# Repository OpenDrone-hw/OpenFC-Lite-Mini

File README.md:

# OpenFC Lite 20x20

Open source Betaflight flight controller built on the RP2354A, 20 x 20 mm
mounting pattern, part of the incutec OpenDrone line.

## Specifications

| | |
|---|---|
| Firmware | Betaflight |
| MCU | RP2354A |
| IMU | BMI270 |
| Barometer | None |
| Blackbox | microSD |
| OSD | Analog and digital |
| UARTs | 3 |
| General-purpose I/O | 4 PWM-capable pins (GPIO22-25) on the 8-pin connector; the Betaflight target runs bidirectional DShot on them |
| RX | External, CRSF or SBUS |
| Input | 3-6S* LiPo (9.0-25.2 V) |
| BEC | 10 V switchable + 5 V always-on, 3 A |
| Current sense | Yes |
| USB | USB-C |
| Mounting | 20 x 20 mm, 3.0 mm holes |
| Dimensions | 26.9 x 26.9 mm |
| PCB | 6-layer, 1.6 mm |

* Also runs on 2S; the 10 V VTX output then follows the battery voltage instead of holding 10 V.

Technical write-up, part list and layout constraints: [AGENTS.md](AGENTS.md).

## Firmware

Betaflight, target `OPENFC_LITE_MINI_RP2350A`. The current image is in
[`firmware/`](firmware/); older ones are in `firmware/archive/`.

Boards flashed before 2026-10-25 show no analog OSD while the LED strip
feature is on, and a WS2812 strip on the LED pad shows wrong colours. The
current image fixes both. To update:

1. In Betaflight Configurator, CLI tab: run `diff all` and save the output.
2. Run `bl rom`. The board reboots as a USB drive named `RP2350`.
3. Copy the `.uf2` from `firmware/` onto that drive. The board restarts on
   its own.
4. Reconnect and check your settings; paste the saved `diff all` back if
   anything is missing.

Without updating, `feature -LED_STRIP` then `save` in the CLI brings the
OSD back (the LED strip is then off).

## In the line

What pairs with what, and what is available:
[opendrone.be](https://opendrone.be).

## Contributing

See [CONTRIBUTING.md](CONTRIBUTING.md).

## License

Hardware licensed under [CERN-OHL-S-2.0](https://ohwr.org/cern_ohl_s_v2.txt),
see [LICENSE](LICENSE).

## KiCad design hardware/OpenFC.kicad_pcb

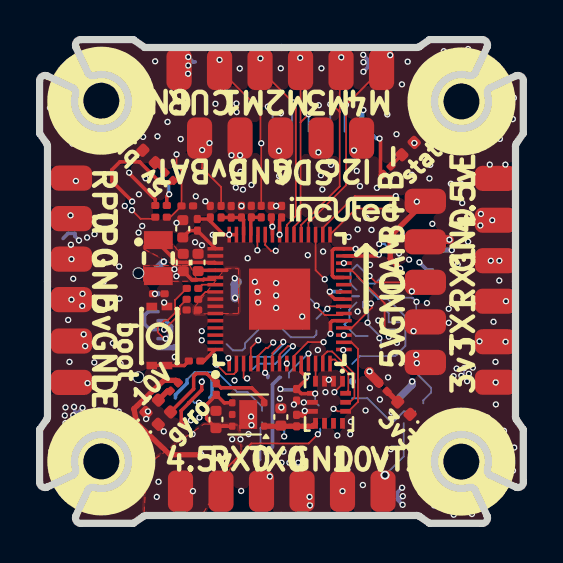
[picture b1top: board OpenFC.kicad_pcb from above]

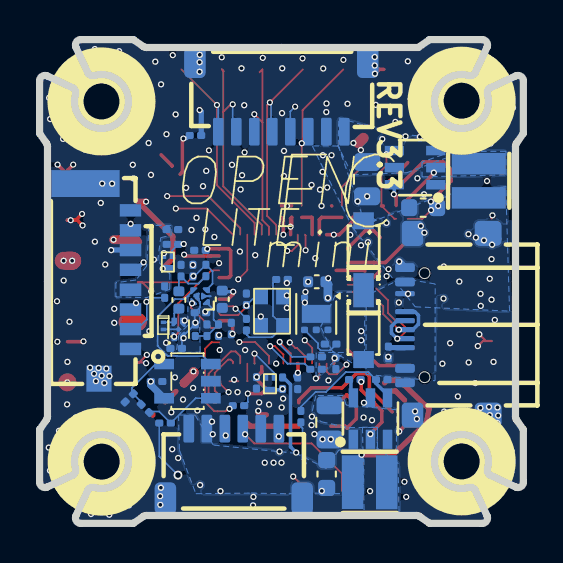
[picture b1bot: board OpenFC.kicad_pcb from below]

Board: 6 copper layers, 26.9 x 26.9 mm, 131 parts (58 on the bottom side), 75 nets.

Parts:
C1, C3, C4, C5, C7, C8, C9, C11, C12, C13, C22, C26, C27, C32, C35, C36, C39, C41, C42, C43: 100n; C_0201_0603Metric
C6, C10: 20p; C_0201_0603Metric
C24, C25: 4.7uF 50v; C_0805_2012Metric
C28, C29: 22uF; C_0603_1608Metric
C31, C37, C44, C45, C46: 4.7uF; C_0402_1005Metric
C33, C34: 22uF; C_0402_1005Metric
C38: 470p; C_0201_0603Metric
C40: 1uF; C_0402_1005Metric
Card1: TF-021B-H265; TF-SMD_TF-021B-H265
D2: LED_1_Blue; LED_0402_1005Metric
D4, D5, D7, D8: LED_1_Green; LED_0402_1005Metric
D6, D10: DSK24; SOD-123_L2.8-W1.8-LS3.7-RD
D9: SDM02U30LP3-7B; X3-DFN0603-2_L0.6-W0.3-RD
J5, J8, J10, J12, J14, J15, J17, J18, J20, J21, J22, J24, J25, J26, J27, J28, J29, J30, J31, J32, J33, J34, J35, J37, J39, J40, J41, J42, J43, J44, J45, J46, J48, J49: 5V; small_pad
L2, L3: XRTC303020D4R7MBCA; IND-SMD_L3.0-W3.0_AFE303020S
L4: AOTA-B201610S3R3-101-T; IND-SMD_L2.0-W1.6_AOTA-B201610S3R3-101-T
P1: SM08B-SRSS-TB(LF)(SN); CONN-TH_SM08B-SRSS-TB-LF-SN
Q5, Q6: AP1606; DFN-3L_L1.0-W0.6-P0.65-BR
R1, R23, R29, R31: 100k; R_0201_0603Metric
R2, R38, R39, R49: 10k; R_0201_0603Metric
R3, R4, R6, R7: 5.1k; R_0201_0603Metric
R5, R9: 1k; R_0201_0603Metric
R15, R24, R37: 30R; R_0201_0603Metric
R30, R34: 6.49k; R_0201_0603Metric
R32: 13.7k; R_0201_0603Metric
R33: 7.5k; R_0201_0603Metric
R36, R46, R47: 510R; R_0201_0603Metric
R41, R48, R52, R53: 75R; R_0201_0603Metric
R42: 3.9k; R_0201_0603Metric
R43: 12k; R_0201_0603Metric
R44: 1.4k; R_0201_0603Metric
R45: 680R; R_0201_0603Metric
R50, R51: 2.4k; R_0201_0603Metric
U1: COS8051SOT; SOT-23-5_L3.0-W1.7-P0.95-LS2.8-BR
U2: TLV7031DPWR; X2SON-4_L0.8-W0.8-P0.48-TL-A
U3, U4: LMR51430YFDDCR; SOT-23-6_L2.9-W1.6-P0.95-LS2.9-BL
U7: LP5912-3.3DRVR; WSON-6-1EP_2x2mm_P0.65mm_EP1x1.6mm
U8: SM06B-SRSS-TB(LF)(SN); CONN-SMD_SM06B-SRSS-TB-LF-SN
U9: BMI270; LGA-14_L3.0-W2.5-P0.50-BR
U10: RP2354A; QFN-60_L7.0-W7.0-P0.40-TL-EP3.4
U11: TS2306A 240GF MSM 9_C2976675; SW-SMD_4P-L3.0-W2.0-P0.85-LS3.5
U12: LP5912-1.8DRVR; WSON-6-1EP_2x2mm_P0.65mm_EP1x1.6mm_ThermalVias
U18: SN74LVC1G3157DTBR; X2SON-6_L1.0-W0.8-BL
USB1: TYPE-C 16P QTWT; USB-TYPE-C-SMD_TYPE-C-16P-QTWT
X1: XTM25012000JT00351001; CRYSTAL-SMD_4P-L2.5-W2.0-BL-A

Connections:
+1.1V: C1.1, C3.1, C37.1, C46.1, L4.1, U10.6 (DVDD), U10.23 (DVDD), U10.39 (DVDD), U10.50 (VREG_FB)
+1.8V_GYRO: C33.1, C35.1, U9.8 (Vdd), U12.1 (OUT)
+3.3V: C5.1, C7.1, C8.1, C9.1, C11.1, C12.1, C13.1, C34.1, C36.1, C39.1, C41.1, C42.1, C43.1, C45.1, Card1.4 (VDD), J28.1 (Pin_1_1), R6.1, R7.1, R15.1, R36.1, R39.1, R43.2, R49.2, U1.5 (+VS), U2.2 (VCC), U7.1 (OUT), U9.5 (Vdd_IO), U10.1 (IOVDD), U10.11 (IOVDD), U10.20 (IOVDD), U10.26 (RUN), U10.30 (IOVDD), U10.38 (IOVDD), U10.44 (ADC_AVDD), U10.45 (IOVDD), U10.49 (VREG_VIN), U10.53 (USB_OTP_VDD), U10.54 (QSPI_IOVDD), U18.5 (VCC)
+4v5: C31.1, C32.1, D6.1 (K), D10.1 (K), J5.1 (Pin_1_1), J40.1 (Pin_1_1), R34.1, U7.4 (EN), U7.6 (IN), U12.4 (EN), U12.6 (IN)
+5V: C29.1, D6.2 (A), J17.1 (Pin_1_1), J22.1 (Pin_1_1), J25.1 (Pin_1_1), J30.1 (Pin_1_1), L3.2, R31.2, R50.1, R51.1
+5V_USB: D10.2 (A), USB1.A4 (VBUS), USB1.A9 (VBUS)
+10V: C28.1, J45.1 (Pin_1_1), L2.2, R29.2, R33.1, U8.1
+BATT: C24.1, C25.1, J29.1 (Pin_1_1), P1.1, R1.2, U3.3 (VIN), U4.3 (VIN), U4.5 (EN)
/BLACKBOX/FLASH_CS: Card1.2 (CD/DAT3), R39.2, U10.33 (GPIO21)
/BLACKBOX/SPI0.MISO: Card1.7 (DAT0), U10.32 (GPIO20)
/BLACKBOX/SPI0.MOSI: Card1.3 (CMD), U10.31 (GPIO19)
/BLACKBOX/SPI0.SCK: Card1.5 (CLX), U10.29 (GPIO18)
/IMU/CS: R49.1, U9.12 (CS), U10.17 (GPIO13)
/IMU/GYRO_INT: U9.4 (INT1), U10.13 (GPIO9)
/IMU/SPI1.MISO: U9.1 (SDO/SA0), U10.16 (GPIO12)
/IMU/SPI1.MOSI: U9.14 (SDA), U10.15 (GPIO11)
/IMU/SPI1.SCK: U9.13 (SCL), U10.14 (GPIO10)
/OSD/OSD_EN: U10.19 (GPIO15), U18.6 (S)
/OSD/OSD_LVL: R42.2, R43.1, R44.2, U18.1 (B2)
/OSD/OSD_SYNC: U2.1 (OUT), U10.27 (GPIO16)
/OSD/OSD_W: R42.1, U10.18 (GPIO14)
/OSD/VIDEO_IN: J32.1 (Pin_1_1), R41.1, R45.2, U18.3 (B1)
/OSD/VIDEO_OUT: J34.1 (Pin_1_1), R48.2
/OSD/VID_DC: C40.2, D9.1 (C), U2.4 (IN+)
/OSD/VID_FILT: C38.1, C40.1, R45.1
/PADS/BUZZER-: J21.1 (Pin_1_1), Q5.3 (D)
/PADS/CURRENT: J33.1 (Pin_1_1), P1.3, R9.1
/PADS/I2C0.SCL: J15.1 (Pin_1_1), R6.2, U10.8 (GPIO5)
/PADS/I2C0.SDA: J18.1 (Pin_1_1), R7.2, U10.7 (GPIO4)
/PADS/LED_STRIP: J10.1 (Pin_1_1), J24.1 (Pin_1_1), Q6.3 (D), R51.2
/PADS/M1: J35.1 (Pin_1_1), P1.5, U10.37 (GPIO25)
/PADS/M2: J37.1 (Pin_1_1), P1.6, U10.36 (GPIO24)
/PADS/M3: J39.1 (Pin_1_1), P1.7, U10.35 (GPIO23)
/PADS/M4: J41.1 (Pin_1_1), P1.8, U10.34 (GPIO22)
/PADS/PIOUART0_TX: J43.1 (Pin_1_1), U10.4 (GPIO2)
/PADS/PU0RX: J44.1 (Pin_1_1), P1.4, U10.5 (GPIO3)
/PADS/U1RX: J8.1 (Pin_1_1), U8.6, U10.10 (GPIO7)
/PADS/UART0_RX: J49.1 (Pin_1_1), U8.4, U10.3 (GPIO1)
/PADS/UART0_TX: J48.1 (Pin_1_1), U8.3, U10.2 (GPIO0)
/PADS/UART1_TX: J12.1 (Pin_1_1), U10.9 (GPIO6)
/POWER/1.8V_PG: D8.2 (A), R34.2, U12.3 (PG)
/POWER/10V_ENABLE: U3.5 (EN), U10.41 (GPIO27_ADC1)
/RP2350A/ADC_VBAT: C4.2, R1.1, R2.2, U10.43 (GPIO29_ADC3)
/RP2350A/BEEPER: Q5.1 (G), R23.2, U10.28 (GPIO17)
/RP2350A/D+: R37.2, USB1.A6 (DP1), USB1.B6 (DP2)
/RP2350A/D-: R24.1, USB1.A7 (DN1), USB1.B7 (DN2)
/RP2350A/ESC_CURR: C22.1, R9.2, U10.42 (GPIO28_ADC2)
/RP2350A/LED0: R52.1, U10.40 (GPIO26_ADC0)
/RP2350A/LED_STRIP_L: Q6.1 (G), U10.12 (GPIO8)
/RP2350A/XIN: C6.2, U10.21 (XIN), X1.1
/RP2350A/XOUT: R5.1, U10.22 (XOUT)
GND: C1.2, C3.2, C4.1, C5.2, C6.1, C7.2, C8.2, C9.2, C10.1, C11.2, C12.2, C13.2, C22.2, C24.2, C25.2, C28.2, C29.2, C31.2, C32.2, C33.2, C34.2, C35.2, C36.2, C37.2, C38.2, C39.2, C41.2, C42.2, C43.2, C44.2, C45.2, C46.2, Card1.6 (VSS), Card1.9, Card1.10, D2.1 (K), D4.1 (K), D5.1 (K), D7.1 (K), D8.1 (K), D9.2 (A), J14.1 (Pin_1_1), J20.1 (Pin_1_1), J26.1 (Pin_1_1), J27.1 (Pin_1_1), J31.1 (Pin_1_1), J42.1 (Pin_1_1), J46.1 (Pin_1_1), P1.2, P1.9, P1.10, Q5.2 (S), Q6.2 (S), R2.1, R3.1, R4.1, R23.1, R30.2, R32.2, R41.2, R44.1, R46.2, U1.2 (-VS), U2.3 (IN-), U2.5 (VEE), U3.1 (GND), U4.1 (GND), U7.3 (GND), U7.5 (PG), U7.7 (EP), U8.2, U8.5, U8.7, U8.8, U9.2 (SDx/AH1/Qvar1), U9.3 (SCx/AH2/Qvar2), U9.6 (GND), U9.7 (GND), U10.47 (VREG_PGND), U10.61 (EP), U11.1, U12.5 (GND), U12.7 (EP), U18.2 (GND), USB1.0 (EH), USB1.A1 (GND), USB1.A12 (GND), X1.2 (GND), X1.4 (GND)
unnamed: C10.2, R5.2, X1.3
unnamed: D2.2 (A), R53.2
unnamed: D4.2 (A), R33.2
unnamed: D5.2 (A), R50.2
unnamed: D7.2 (A), R36.2
unnamed: R38.1, U11.2
unnamed: R52.2, R53.1
unnamed: U1.3 (IN+), U18.4 (A)
unnamed: R46.1, R47.1, U1.4 (IN-)
unnamed: R47.2, R48.1, U1.1 (OUT)
unnamed: C26.2, U3.6 (CB)
unnamed: R29.1, R30.1, U3.4 (FB)
unnamed: C26.1, L2.1, U3.2 (SW)
unnamed: C27.2, U4.6 (CB)
unnamed: R31.1, R32.1, U4.4 (FB)
unnamed: C27.1, L3.1, U4.2 (SW)
unnamed: R38.2, U10.60 (QSPI_SS)
unnamed: R24.2, U10.51 (USB_DM)
unnamed: R37.1, U10.52 (USB_DP)
unnamed: C44.1, R15.2, U10.46 (VREG_AVDD)
unnamed: L4.2, U10.48 (VREG_LX)
unnamed: R3.2, USB1.A5 (CC1)
unnamed: R4.2, USB1.B5 (CC2)

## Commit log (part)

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2026-06-02 many tiny improvements
    - I/O correctness
    - SPI0/SPI1/I2C0 bus corrections
    - decoupling of DVDD
    - ADC_AVDD as per RPi documents
    - removal of SBUS
    - connect ESC serial
2026-06-03 RP2354A
2026-06-03 piu1
2026-06-03 switch spi
2026-06-03 routex2
2026-06-03 some minor tweaks
    - remove some unnecessary resistors
    - slightly higher 10V rail to account for voltage drop
    - some cleanup
    - simpler PG 1.8V circuit
2026-06-03 LED resistors
    Also reduced the amount of different resistors for cheaper assembly
2026-06-03 remove some unneeded decoupling caps from RP2350
2026-06-03 update MOSFET part numbers
2026-06-04 ROUTE
2026-06-04 clean libs
2026-06-04 details
2026-06-04 led names
2026-06-05 Clean routing
